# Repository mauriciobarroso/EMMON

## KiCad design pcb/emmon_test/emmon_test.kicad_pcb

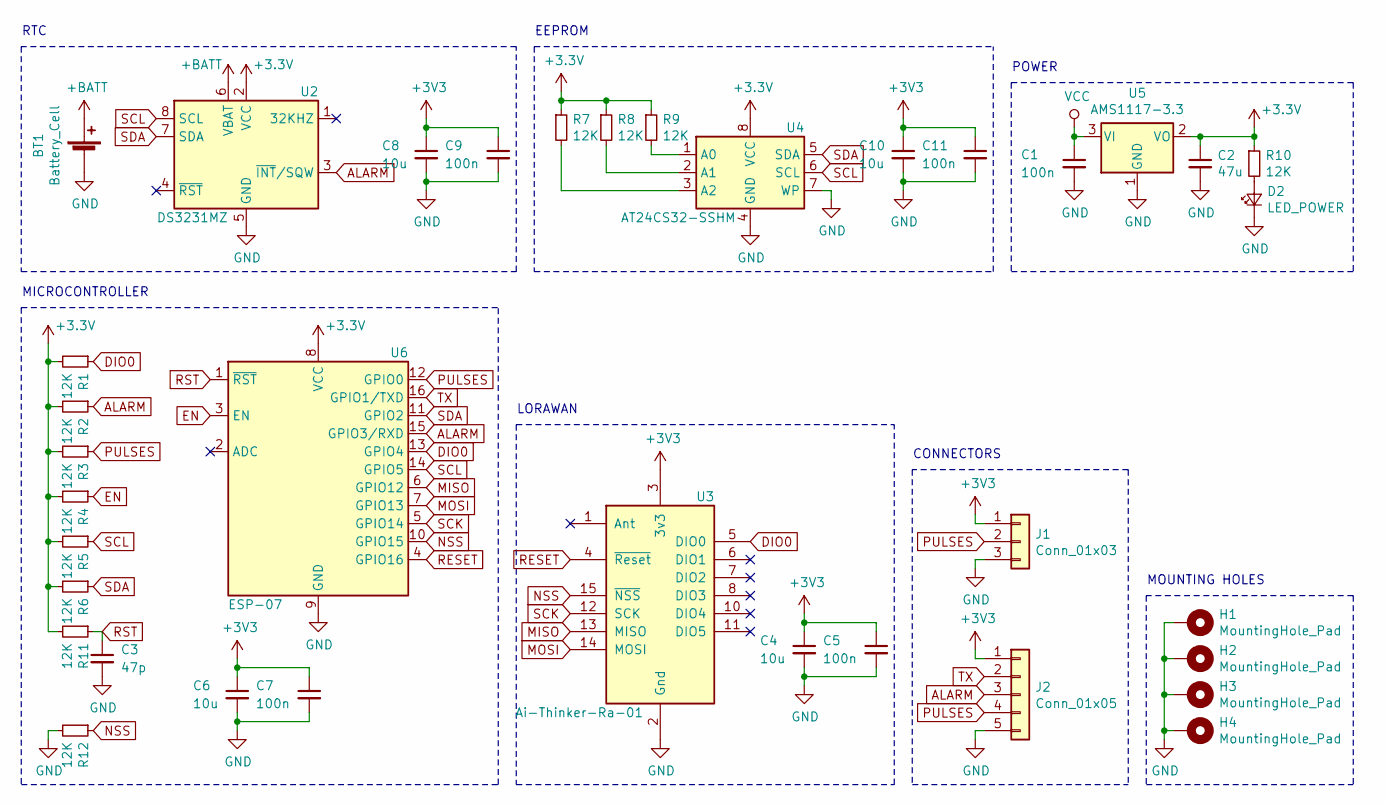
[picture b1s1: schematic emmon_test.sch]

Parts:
BT1: Battery_Cell; BatteryHolder_Keystone_3002_1x2032
C1, C5, C7, C9, C11: 100n; C_0805_2012Metric
C2: 47u; C_0805_2012Metric
C3: 47p; C_0805_2012Metric
C4, C6, C8, C10: 10u; C_0805_2012Metric
D2: LED_POWER; LED_0805_2012Metric
H1, H2, H3, H4: MountingHole_Pad; MountingHole_4.3mm_M4_Pad_Via
J1: Conn_01x03; PinHeader_1x03_P2.54mm_Vertical
J2: Conn_01x05; PinHeader_1x05_P2.54mm_Vertical
R1, R2, R3, R4, R5, R6, R7, R8, R9, R10, R11, R12: 12K; R_0805_2012Metric
U2: DS3231MZ; SOIC-8_3.9x4.9mm_P1.27mm
U3: Ai-Thinker-Ra-01; Ai-Thinker-Ra-01-LoRa
U4: AT24CS32-SSHM; SOIC-8_3.9x4.9mm_P1.27mm
U5: AMS1117-3.3; SOT-223-3_TabPin2
U6: ESP-07

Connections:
+BATT: BT1.1 (+), U2.6 (VBAT)
ALARM: J2.3, R2.1, U2.3 (~INT~/SQW), U6.15 (GPIO3/RXD)
DIO0: R1.1, U3.5 (DIO0), U6.13 (GPIO4)
EN: R4.1, U6.3 (EN)
GND: BT1.2 (-), C1.2, C2.2, C3.2, C4.2, C5.2, C6.2, C7.2, C8.2, C9.2, C10.2, C11.2, D2.1 (K), H1.1, H2.1, H3.1, H4.1, J1.3, J2.5, R12.2, U2.5 (GND), U3.2 (Gnd), U3.9 (Gnd), U3.16 (Gnd), U4.4 (GND), U4.7 (WP), U5.1 (GND), U6.9 (GND)
MISO: U3.13 (MISO), U6.6 (GPIO12)
MOSI: U3.14 (MOSI), U6.7 (GPIO13)
NSS: R12.1, U3.15 (~NSS), U6.10 (GPIO15)
unnamed: D2.2 (A), R10.2
unnamed: R7.2, U4.3 (A2)
unnamed: R8.2, U4.2 (A1)
unnamed: R9.2, U4.1 (A0)
PULSES: J1.2, J2.4, R3.1, U6.12 (GPIO0)
RESET: U3.4 (~Reset), U6.4 (GPIO16)
RST: C3.1, R11.1, U6.1 (~RST)
SCK: U3.12 (SCK), U6.5 (GPIO14)
SCL: R5.1, U2.8 (SCL), U4.6 (SCL), U6.14 (GPIO5)
SDA: R6.1, U2.7 (SDA), U4.5 (SDA), U6.11 (GPIO2)
TX: J2.2, U6.16 (GPIO1/TXD)
VCC: C1.1, U5.3 (VI)

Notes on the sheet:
POWER
EEPROM
RTC
MOUNTING HOLES
LORAWAN
CONNECTORS
MICROCONTROLLER

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
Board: 2 copper layers, 36 parts (0 on the bottom side), 21 nets, no tracks yet.

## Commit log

2020-04-04 se agregan achivos del proyecto
2020-04-17 se implementa web server
2020-05-08 se implementa oop en el codigo y se edita el pcb
2020-05-08 se cambia de directorio
2020-05-13 se actualiza .gitignore
2020-05-13 se mejora web server
2020-05-13 se edita.gitignore
2020-05-13 se modifica la longitud de spiffs
2020-05-14 se agrega modo debug
2020-05-14 se agregan secciones críticas y se mejora la apariencia del código
2020-05-14 se agregan archivos de SPIFFS
2020-05-14 se modifica el tamaño de SPIFFS
2020-05-14 se elimina sdkconfig.defaults
2020-05-14 se elimina sdkconfig y sdkconfig.old
2020-05-14 se elimina .settings
2020-05-14 se eliminan archivos innecesarios
2020-05-14 se modifican cosas menores
2020-05-18 se agregan archivos para la eeprom
2020-05-18 se cambia el nombre de at24c32 a at24cx
2020-05-18 se cambia el delay de escritura de 5 ms a 10 ms
2020-05-18 se modifican las funciones para reducir código
2020-05-18 se quietan elementos a la estructura data_logger_t
2020-05-18 se edita README.md
2020-05-24 se cambian de nombre algunos archivos
2020-05-24 se modifican los archivos de spiffs
2020-05-24 se crean los archivos para spiffs y wifi
2020-05-24 se agrega función de recepción
2020-05-24 se agrega función para obtener el log histórico
2020-05-24 se quitan los archivos wifi y spiffs
2020-05-24 se cambia el nombre de lora_parsePacket a lora_parse_packet
2020-05-24 se modifica el orden de algunas líneas de código
2020-08-05 se modifican las librerías data_logger, data_communication y web_server
2020-08-06 se reordena el código y se crea emmon.c
2020-08-08 se modifican los nombres de los archivos
2020-08-11 se modifica .gitignore y se mejora el filtro de pulsos
2020-09-11 se realizan cambios menores
